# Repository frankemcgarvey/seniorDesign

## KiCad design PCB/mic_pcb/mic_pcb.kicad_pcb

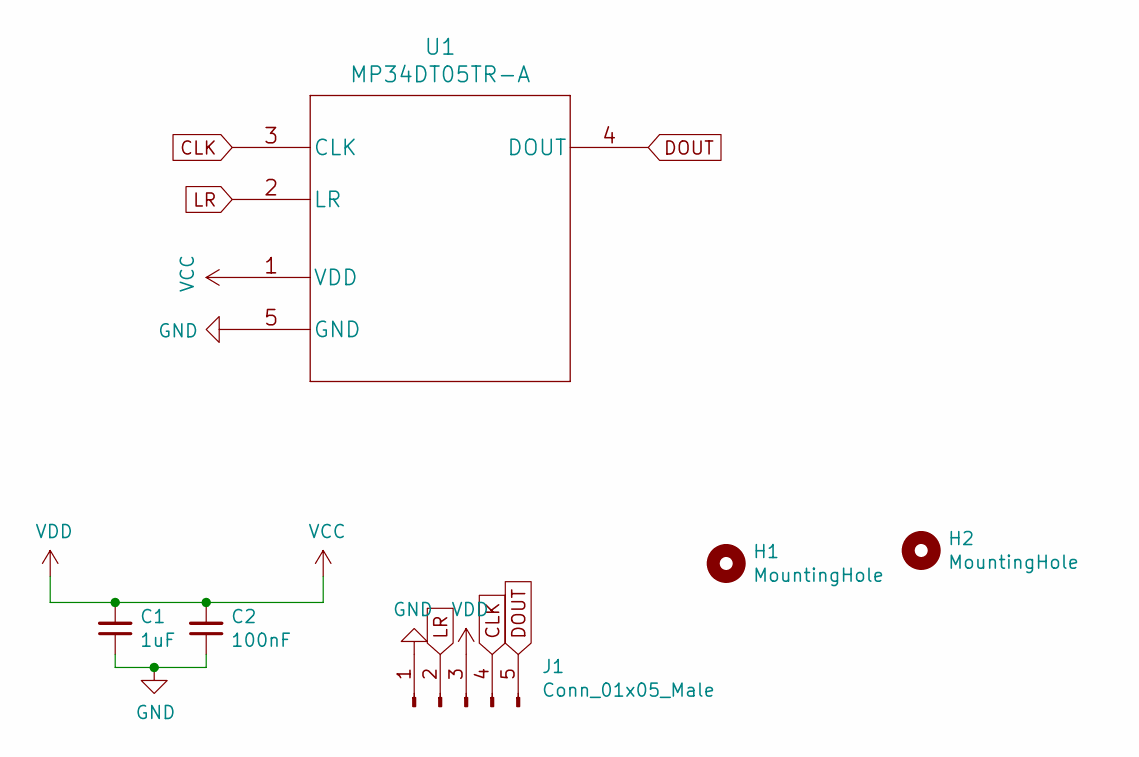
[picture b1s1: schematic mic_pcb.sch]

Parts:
C1: 1uF; C_0402_1005Metric; LCSC Part # C52923
C2: 100nF; C_0402_1005Metric; LCSC Part # C1525
H1, H2: MountingHole; MountingHole_2.2mm_M2_Pad_Via
J1: Conn_01x05_Male; PinHeader_1x05_P2.54mm_Vertical
U1: MP34DT05TR-A

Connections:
CLK: J1.4, U1.3 (CLK)
DOUT: J1.5, U1.4 (DOUT)
GND: C1.1, C2.1, J1.1, U1.5 (GND)
LR: J1.2, U1.2 (LR)
VCC: C1.2, C2.2, J1.3, U1.1 (VDD)

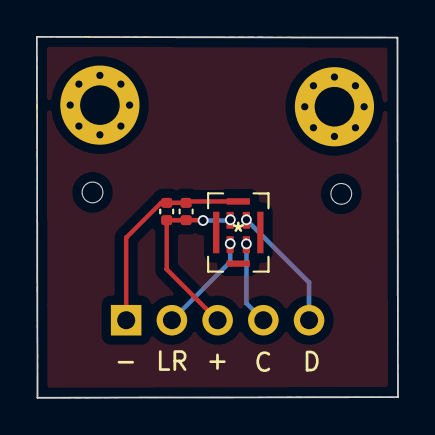
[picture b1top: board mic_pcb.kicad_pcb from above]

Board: 2 copper layers, 20.1 x 20.0 mm, 6 parts (0 on the bottom side), 5 nets.

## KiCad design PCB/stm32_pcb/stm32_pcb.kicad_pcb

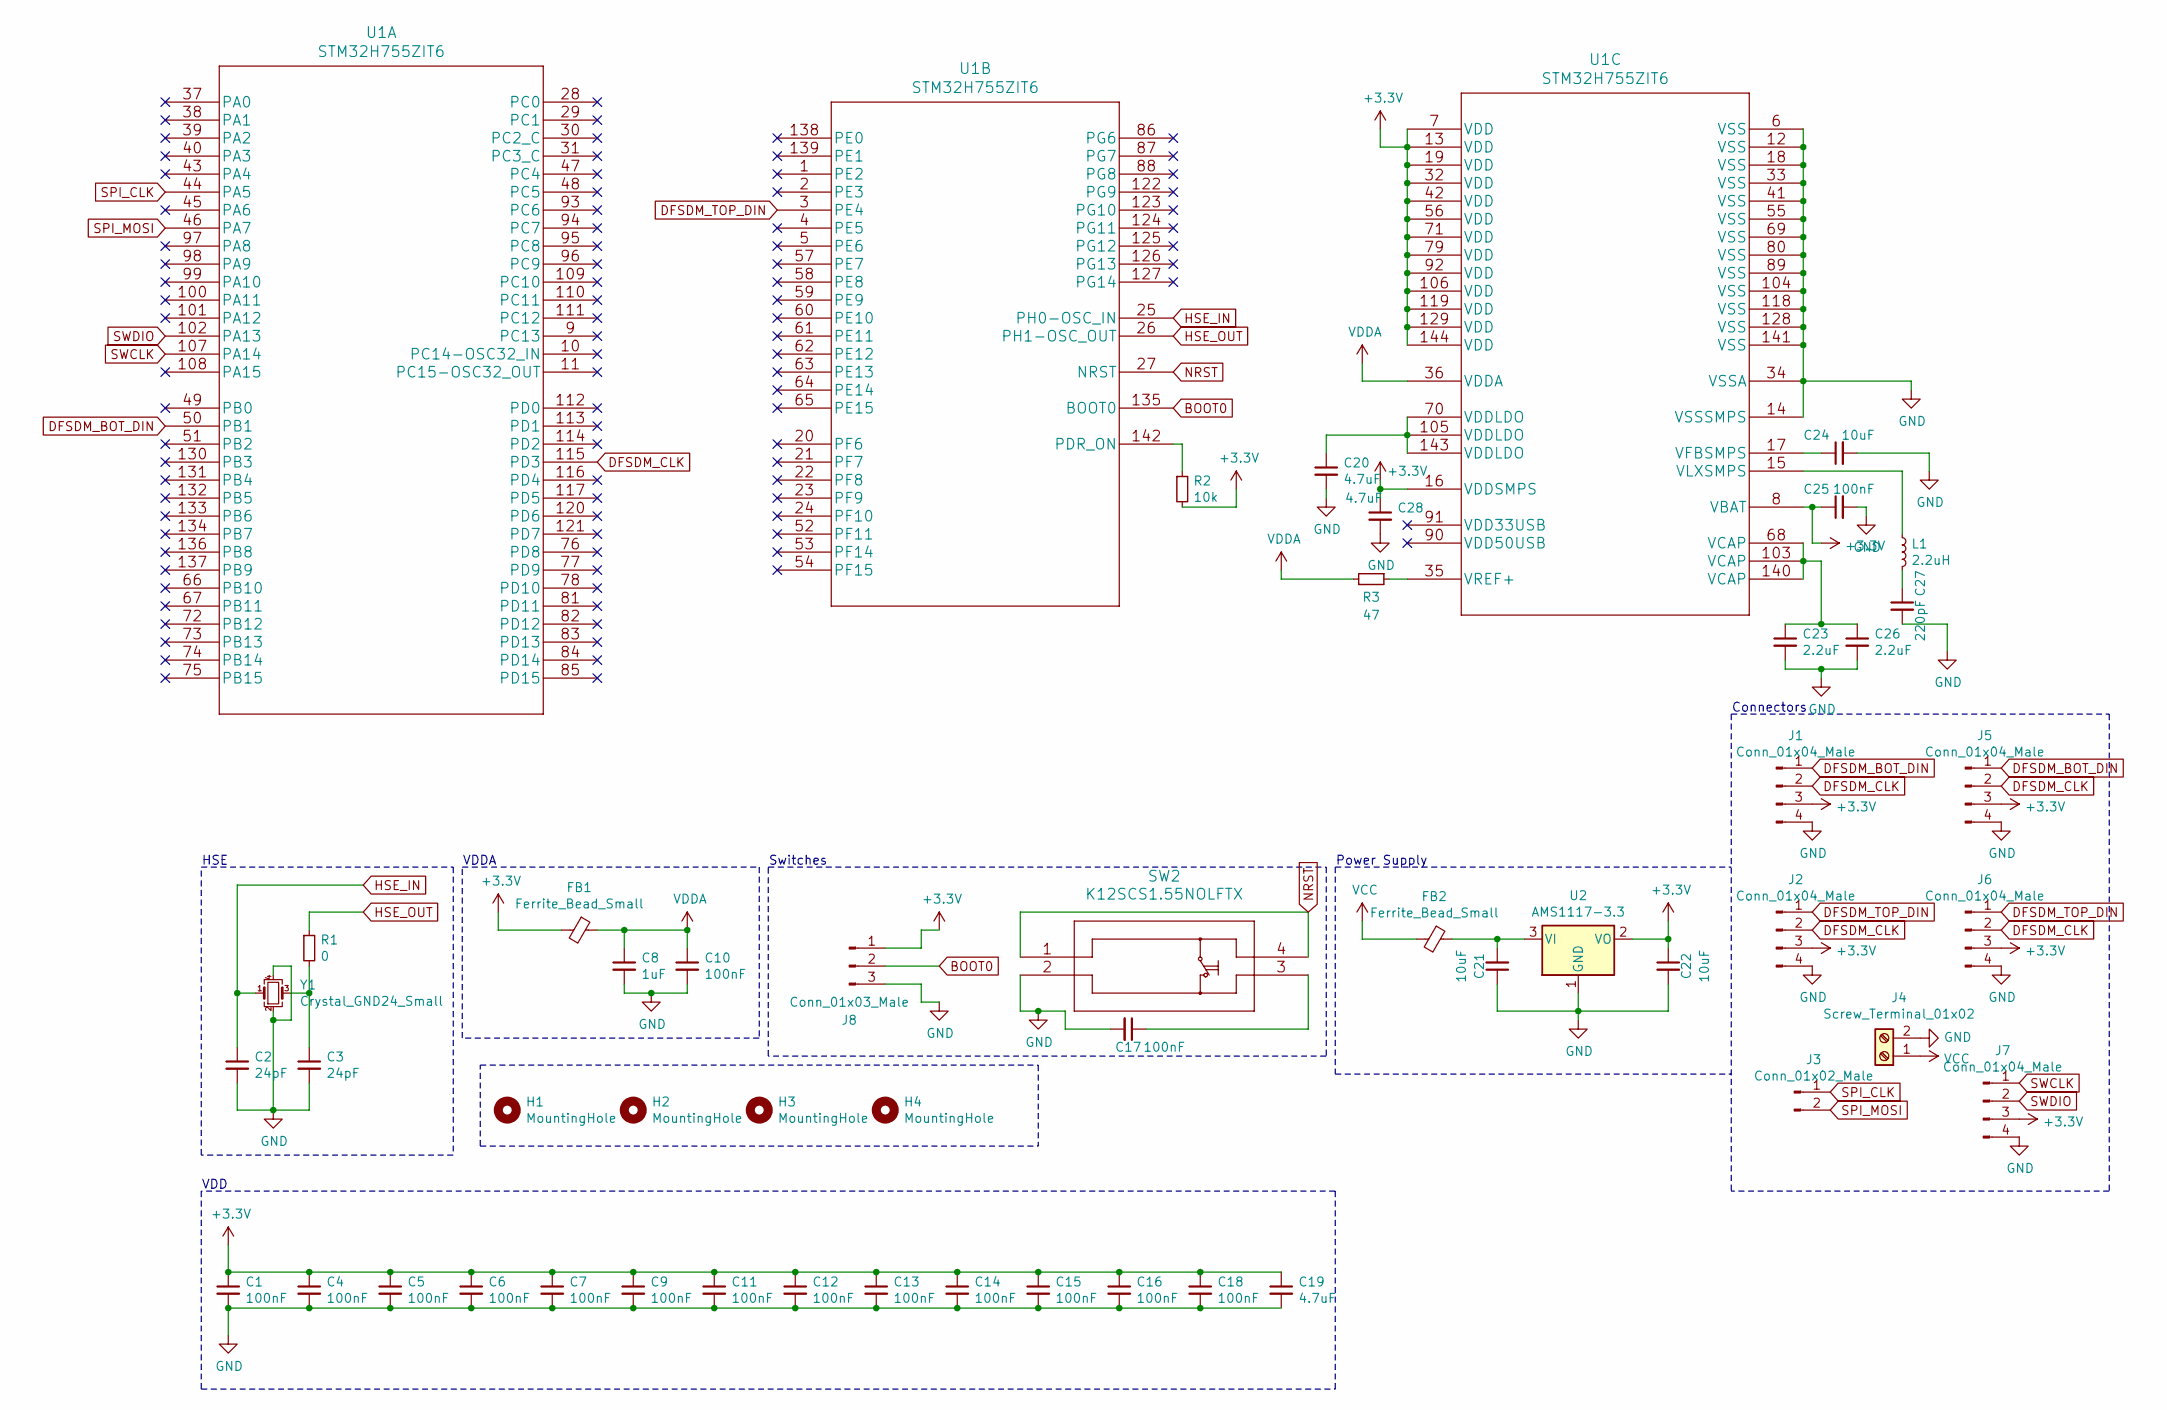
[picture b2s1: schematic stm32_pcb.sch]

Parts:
C1, C4, C5, C6, C7, C9, C10, C11, C12, C13, C14, C15, C16, C17, C18, C25: 100nF; C_0402_1005Metric; LCSC Part # C1525
C2, C3: 24pF; C_0402_1005Metric; LCSC Part # C22728
C8: 1uF; C_0402_1005Metric; LCSC Part # C52923
C19, C20, C28: 4.7uF; C_0402_1005Metric; LCSC Part # C23733
C21, C22: 10uF; C_0805_2012Metric; LCSC Part # C15850
C23, C26: 2.2uF; C_0402_1005Metric; LCSC Part # C12530
C24: 10uF; C_0402_1005Metric; LCSC Part # C15525
C27: 220pF; C_0402_1005Metric; LCSC Part # C1530
FB1, FB2: Ferrite_Bead_Small; L_0805_2012Metric; LCSC Part # C1015
H1, H2, H3, H4: MountingHole; MountingHole_4.3mm_M4_Pad_Via
J1, J2, J5, J6, J7: Conn_01x04_Male; PinHeader_1x04_P2.54mm_Vertical
J3: Conn_01x02_Male; PinHeader_1x02_P2.54mm_Vertical
J4: Screw_Terminal_01x02; TerminalBlock_Phoenix_PT-1,5-2-3.5-H_1x02_P3.50mm_Horizontal
J8: Conn_01x03_Male; PinHeader_1x03_P2.54mm_Vertical
L1: 2.2uH; L_0805_2012Metric; LCSC Part # C1043
R1: 0; R_0402_1005Metric; LCSC Part # C17168
R2: 10k; R_0402_1005Metric; LCSC Part # C25744
R3: 47; R_0402_1005Metric; LCSC Part # C25118
SW2: K12SCS1.55NOLFTX
U1: STM32H755ZIT6
U2: AMS1117-3.3; SOT-223-3_TabPin2; LCSC Part # C6186
Y1: Crystal_GND24_Small; OSC_ABM3B-8.000MHZ-B2-T; LCSC Part # C83312

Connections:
+3V3: C1.1, C4.1, C5.1, C6.1, C7.1, C9.1, C11.1, C12.1, C13.1, C14.1, C15.1, C16.1, C18.1, C19.1, C22.1, C25.1, C28.1, FB1.2, J1.3, J2.3, J5.3, J6.3, J7.3, J8.1, R2.2, U1.7 (VDD), U1.8 (VBAT), U1.13 (VDD), U1.16 (VDDSMPS), U1.19 (VDD), U1.32 (VDD), U1.42 (VDD), U1.56 (VDD), U1.71 (VDD), U1.79 (VDD), U1.92 (VDD), U1.106 (VDD), U1.119 (VDD), U1.129 (VDD), U1.144 (VDD), U2.2 (VO)
BOOT0: J8.2, U1.135 (BOOT0)
DFSDM_BOT_DIN: J1.1, J5.1, U1.50 (PB1)
DFSDM_CLK: J1.2, J2.2, J5.2, J6.2, U1.115 (PD3)
DFSDM_TOP_DIN: J2.1, J6.1, U1.3 (PE4)
GND: C1.2, C2.2, C3.2, C4.2, C5.2, C6.2, C7.2, C8.2, C9.2, C10.2, C11.2, C12.2, C13.2, C14.2, C15.2, C16.2, C17.2, C18.2, C19.2, C20.2, C21.1, C22.2, C23.2, C24.2, C25.2, C26.2, C27.2, C28.2, J1.4, J2.4, J4.2, J5.4, J6.4, J7.4, J8.3, SW2.2, U1.6 (VSS), U1.12 (VSS), U1.14 (VSSSMPS), U1.18 (VSS), U1.33 (VSS), U1.34 (VSSA), U1.41 (VSS), U1.55 (VSS), U1.69 (VSS), U1.80 (VSS), U1.89 (VSS), U1.104 (VSS), U1.118 (VSS), U1.128 (VSS), U1.141 (VSS), U2.1 (GND), Y1.2, Y1.4
HSE_IN: C2.1, U1.25 (PH0-OSC_IN), Y1.1
HSE_OUT: R1.1, U1.26 (PH1-OSC_OUT)
NRST: SW2.1, SW2.4, U1.27 (NRST)
unnamed: C3.1, R1.2, Y1.3
unnamed: C17.1, SW2.3
unnamed: C20.1, U1.70 (VDDLDO), U1.105 (VDDLDO), U1.143 (VDDLDO)
unnamed: C21.2, FB2.1, U2.3 (VI)
unnamed: C23.1, C26.1, U1.68 (VCAP), U1.103 (VCAP), U1.140 (VCAP)
unnamed: C24.1, U1.17 (VFBSMPS)
unnamed: C27.1, L1.2
unnamed: L1.1, U1.15 (VLXSMPS)
unnamed: R2.1, U1.142 (PDR_ON)
unnamed: R3.1, U1.35 (VREF+)
SPI_CLK: J3.1, U1.44 (PA5)
SPI_MOSI: J3.2, U1.46 (PA7)
SWCLK: J7.1, U1.107 (PA14)
SWDIO: J7.2, U1.102 (PA13)
VCC: FB2.2, J4.1
VDDA: C8.1, C10.1, FB1.1, R3.2, U1.36 (VDDA)

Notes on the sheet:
HSE
VDDA
Switches
VDD
Power Supply
Connectors

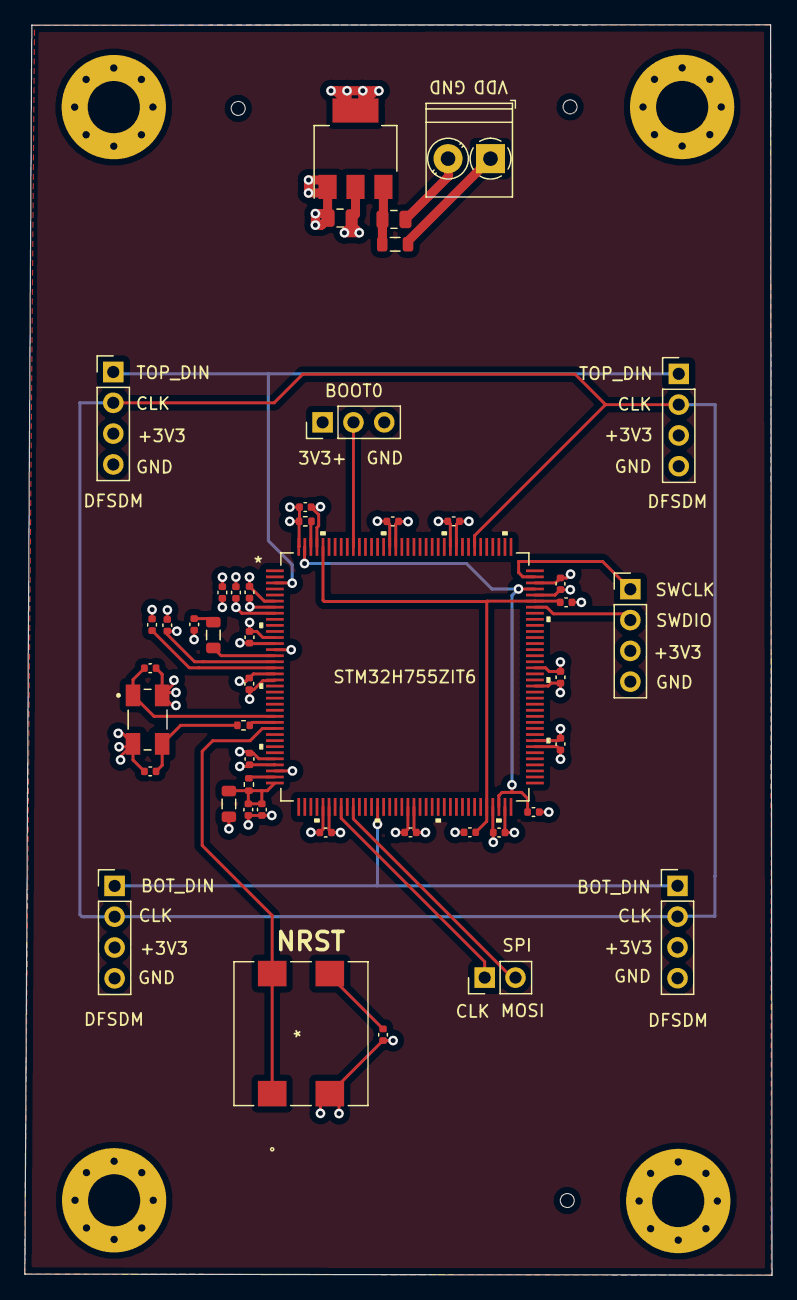
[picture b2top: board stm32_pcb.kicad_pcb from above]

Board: 4 copper layers, 61.6 x 103.1 mm, 50 parts (0 on the bottom side), 25 nets.

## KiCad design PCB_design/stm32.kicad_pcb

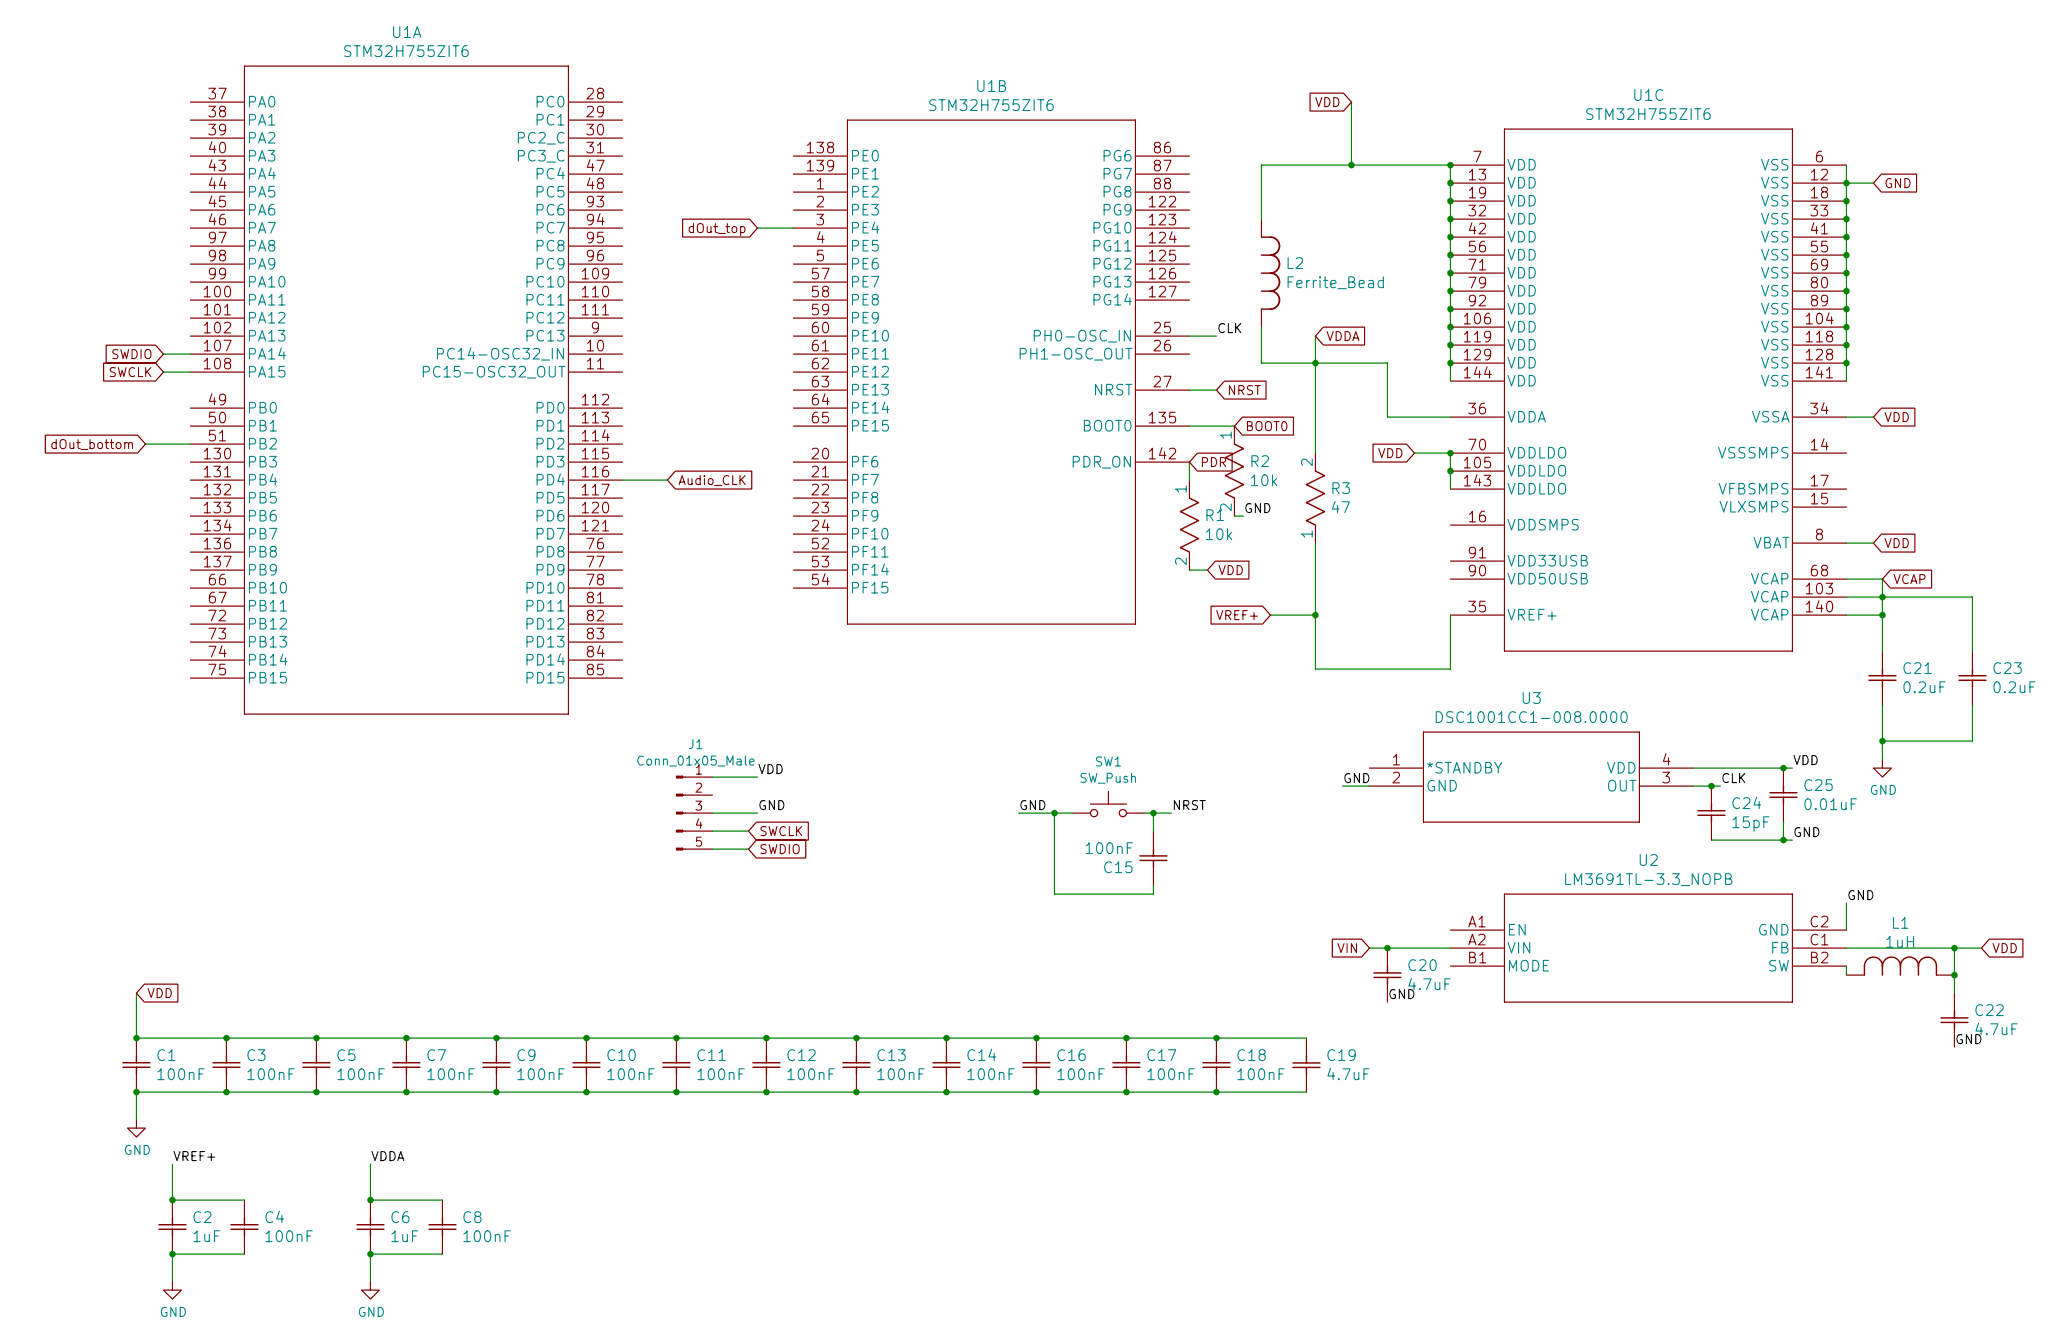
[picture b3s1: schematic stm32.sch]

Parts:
C1, C3, C4, C5, C7, C8, C9, C10, C11, C12, C13, C14, C15, C16, C17, C18: 100nF; C0201C104K9PACTU
C2, C6: 1uF; CKG57KX7R2E105K335JH
C19, C20, C22: 4.7uF; CKG57KX7R2A475K335JH
C21, C23: 0.2uF; CAA572C0G2J204J640LH
C24: 15pF; 600S150FT250XT
C25: 0.01uF; GRM2195C1H113JA01D
J1: Conn_01x05_Male; PinHeader_1x05_P1.00mm_Vertical
L1: 1uH; 74438336010
L2: Ferrite_Bead; MMZ1608B601CTAH0
R1, R2: 10k; RMCF0201FT10K0
R3: 47; RC0603FR-0747RL
SW1: SW_Push; Panasonic_EVQPUJ_EVQPUA
U1: STM32H755ZIT6
U2: LM3691TL-3.3_NOPB; LM3691TL-3.3&slash_NOPB
U3: DSC1001CC1-008.0000

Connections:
/CLK: C24.1, U1.25 (PH0-OSC_IN), U3.3 (OUT)
Audio_CLK: U1.116 (PD4)
BOOT0: R2.1, U1.135 (BOOT0)
GND: C1.2, C2.2, C3.2, C4.2, C5.2, C6.2, C7.2, C8.2, C9.2, C10.2, C11.2, C12.2, C13.2, C14.2, C15.1, C16.2, C17.2, C18.2, C19.1, C20.1, C21.2, C22.1, C23.2, C24.2, C25.2, J1.3, R2.2, SW1.1, U1.6 (VSS), U1.12 (VSS), U1.18 (VSS), U1.33 (VSS), U1.41 (VSS), U1.55 (VSS), U1.69 (VSS), U1.80 (VSS), U1.89 (VSS), U1.104 (VSS), U1.118 (VSS), U1.128 (VSS), U1.141 (VSS), U2.C2 (GND), U3.2 (GND)
NRST: C15.2, SW1.2, U1.27 (NRST)
unnamed: L1.2, U2.B2 (SW)
unnamed: R1.1, U1.142 (PDR_ON)
SWCLK: J1.4, U1.108 (PA15)
SWDIO: J1.5, U1.107 (PA14)
VCAP: C21.1, C23.1, U1.68 (VCAP), U1.103 (VCAP), U1.140 (VCAP)
VDD: C1.1, C3.1, C5.1, C7.1, C9.1, C10.1, C11.1, C12.1, C13.1, C14.1, C16.1, C17.1, C18.1, C19.2, C22.2, C25.1, J1.1, L1.1, L2.2, R1.2, U1.7 (VDD), U1.8 (VBAT), U1.13 (VDD), U1.19 (VDD), U1.32 (VDD), U1.34 (VSSA), U1.42 (VDD), U1.56 (VDD), U1.70 (VDDLDO), U1.71 (VDD), U1.79 (VDD), U1.92 (VDD), U1.105 (VDDLDO), U1.106 (VDD), U1.119 (VDD), U1.129 (VDD), U1.143 (VDDLDO), U1.144 (VDD), U2.C1 (FB), U3.4 (VDD)
VDDA: C6.1, C8.1, L2.1, R3.2, U1.36 (VDDA)
VIN: C20.2, U2.A2 (VIN)
VREF+: C2.1, C4.1, R3.1, U1.35 (VREF+)
dOut_bottom: U1.51 (PB2)
dOut_top: U1.3 (PE4)

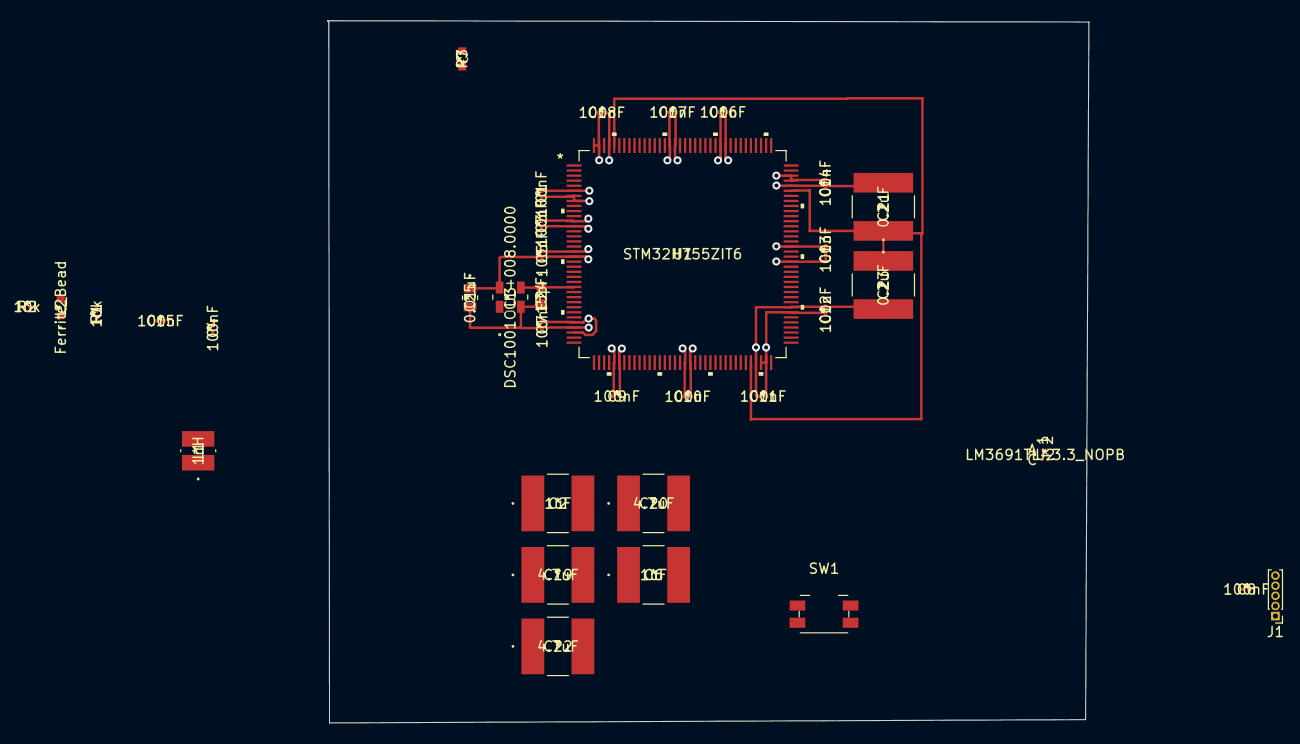
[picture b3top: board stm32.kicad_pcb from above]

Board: 4 copper layers, 75.2 x 69.3 mm, 35 parts (0 on the bottom side), 13 nets.

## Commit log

2021-06-17 UART/SAI/PDM2PCM Implemented; more testing is needed
2021-06-19 Implemented pcmtowav
2021-06-23 Mic Testing Ready; configured for 10 secs of uploading through UART
2021-06-23 Correct amount of bytes are transfered; more testing needed
2021-06-23 UART_DMA appears to NOT hang up while transmitting like calculations stated; there should be no bottle neck between SAI_RECEIVE_DMA & PDM2PCM & UART_SEND_DMA; going to test UART->PC data exchange
2021-06-23 UART->PC transfers correct amount of bytes; next testing is actual mics with 2 channels (i.e. 2 mics)
2021-06-25 Fixed Cache Sizes for Clean/Invalidate
2021-06-25 Fixed pcm buffer size
2021-06-26 Working project for 2 mics, testing of 4 mics needed
2021-06-29 Made code more generic with CHANNEL_NUMBER
2021-06-30 4 Mics Work; onto filtering the mics for better quality
2021-07-03 CMSIS DSP Library Implemented
2021-07-08 Checkpoint: Working On GCC-PHAT; Need to make sure to change code to match new filter function
2021-07-20 Adding gccphat.py
2021-07-21 Updated portability of code, created input variables
2021-07-21 Added inter variable for input for gccphat
2021-07-22 Added test PCM files in pcmFiles
2021-07-22 Fixed error in pcm2wav
2021-07-26 Fixed FIR Filter Implementation, no noise is detedted now, bandpass FFT shows that the range is between 1k-2k
2021-08-01 Converted to float only
2021-08-10 Checkpoint
2021-08-17 DFSDM Checkpoint
2021-09-11 Checkpoint 9/11
2021-11-12 Checkpoint 11/12

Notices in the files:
parts and their libraries:
Copyright 2021 Accelerated Designs. All rights reserved.
